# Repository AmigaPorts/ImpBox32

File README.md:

# ImpBox32

<center></center>

This device provides wireless connectivity to your Amiga.
The primary purpose is for use with [IMP](http://aminet.net/package/mus/play/imp3), but with proper firmware it can act as general-purpose network interface.

## Using the IMP firmware

### Flashing the device

Flash the device with firmware from `firmware_impbox` directory - you can use RX/TX pin header for this using typical ESP32 tooling.
Assuming that your COM port is /dev/ttyUSB0:

```plain
esptool --chip esp32 --port /dev/ttyUSB0 --baud 921600 --before default_reset --after hard_reset write_flash -z --flash_mode dio --flash_freq 80m --flash_size 4MB \
0x1000 bootloader.bin \
0x8000 partitions.bin \
0xe000 boot_app0.bin \
0x10000 fw_36.bin
```

The IMP firmware automatically updates itself, so you need to flash it manually only once.

### Using with IMP3

The firmware makes use of SD1306 or compatible OLED I2C display - be sure to connect one at least during registration and configuration phase.

The IMP firmware requires inputing registration key.
If you've built the device for yourself, contact Juen on EAB for getting one.
If you're considering building and selling a batch of devices, ask Juen first to discuss terms on getting keys for them.
See messages displayed on OLED for detailed instructions on how to enter your key.

to configure WiFi network, use following commands:

```plain
imp3 ibcs your_ssid
imp3 ibcp your_password
imp3 ibcc your_key
```

Device stores the key as well as network parameters in its flash memory, hence configuration needs to be done only once.
Once configured, to launch IMP, type:

```plain
imp3 ib
```

## Differences between PCB revisions

Be sure to use the latest PCB revision - old ones are buggy and not supported.

The board currently recommended by IMP authors is rev3.
There's also rev3s board with SD card slot which cauld be made to work with modified sdbox firmware, and will be eventually suported by the universal firmware.

## Using the universal firmware

TBD - this firmware is currently not available.

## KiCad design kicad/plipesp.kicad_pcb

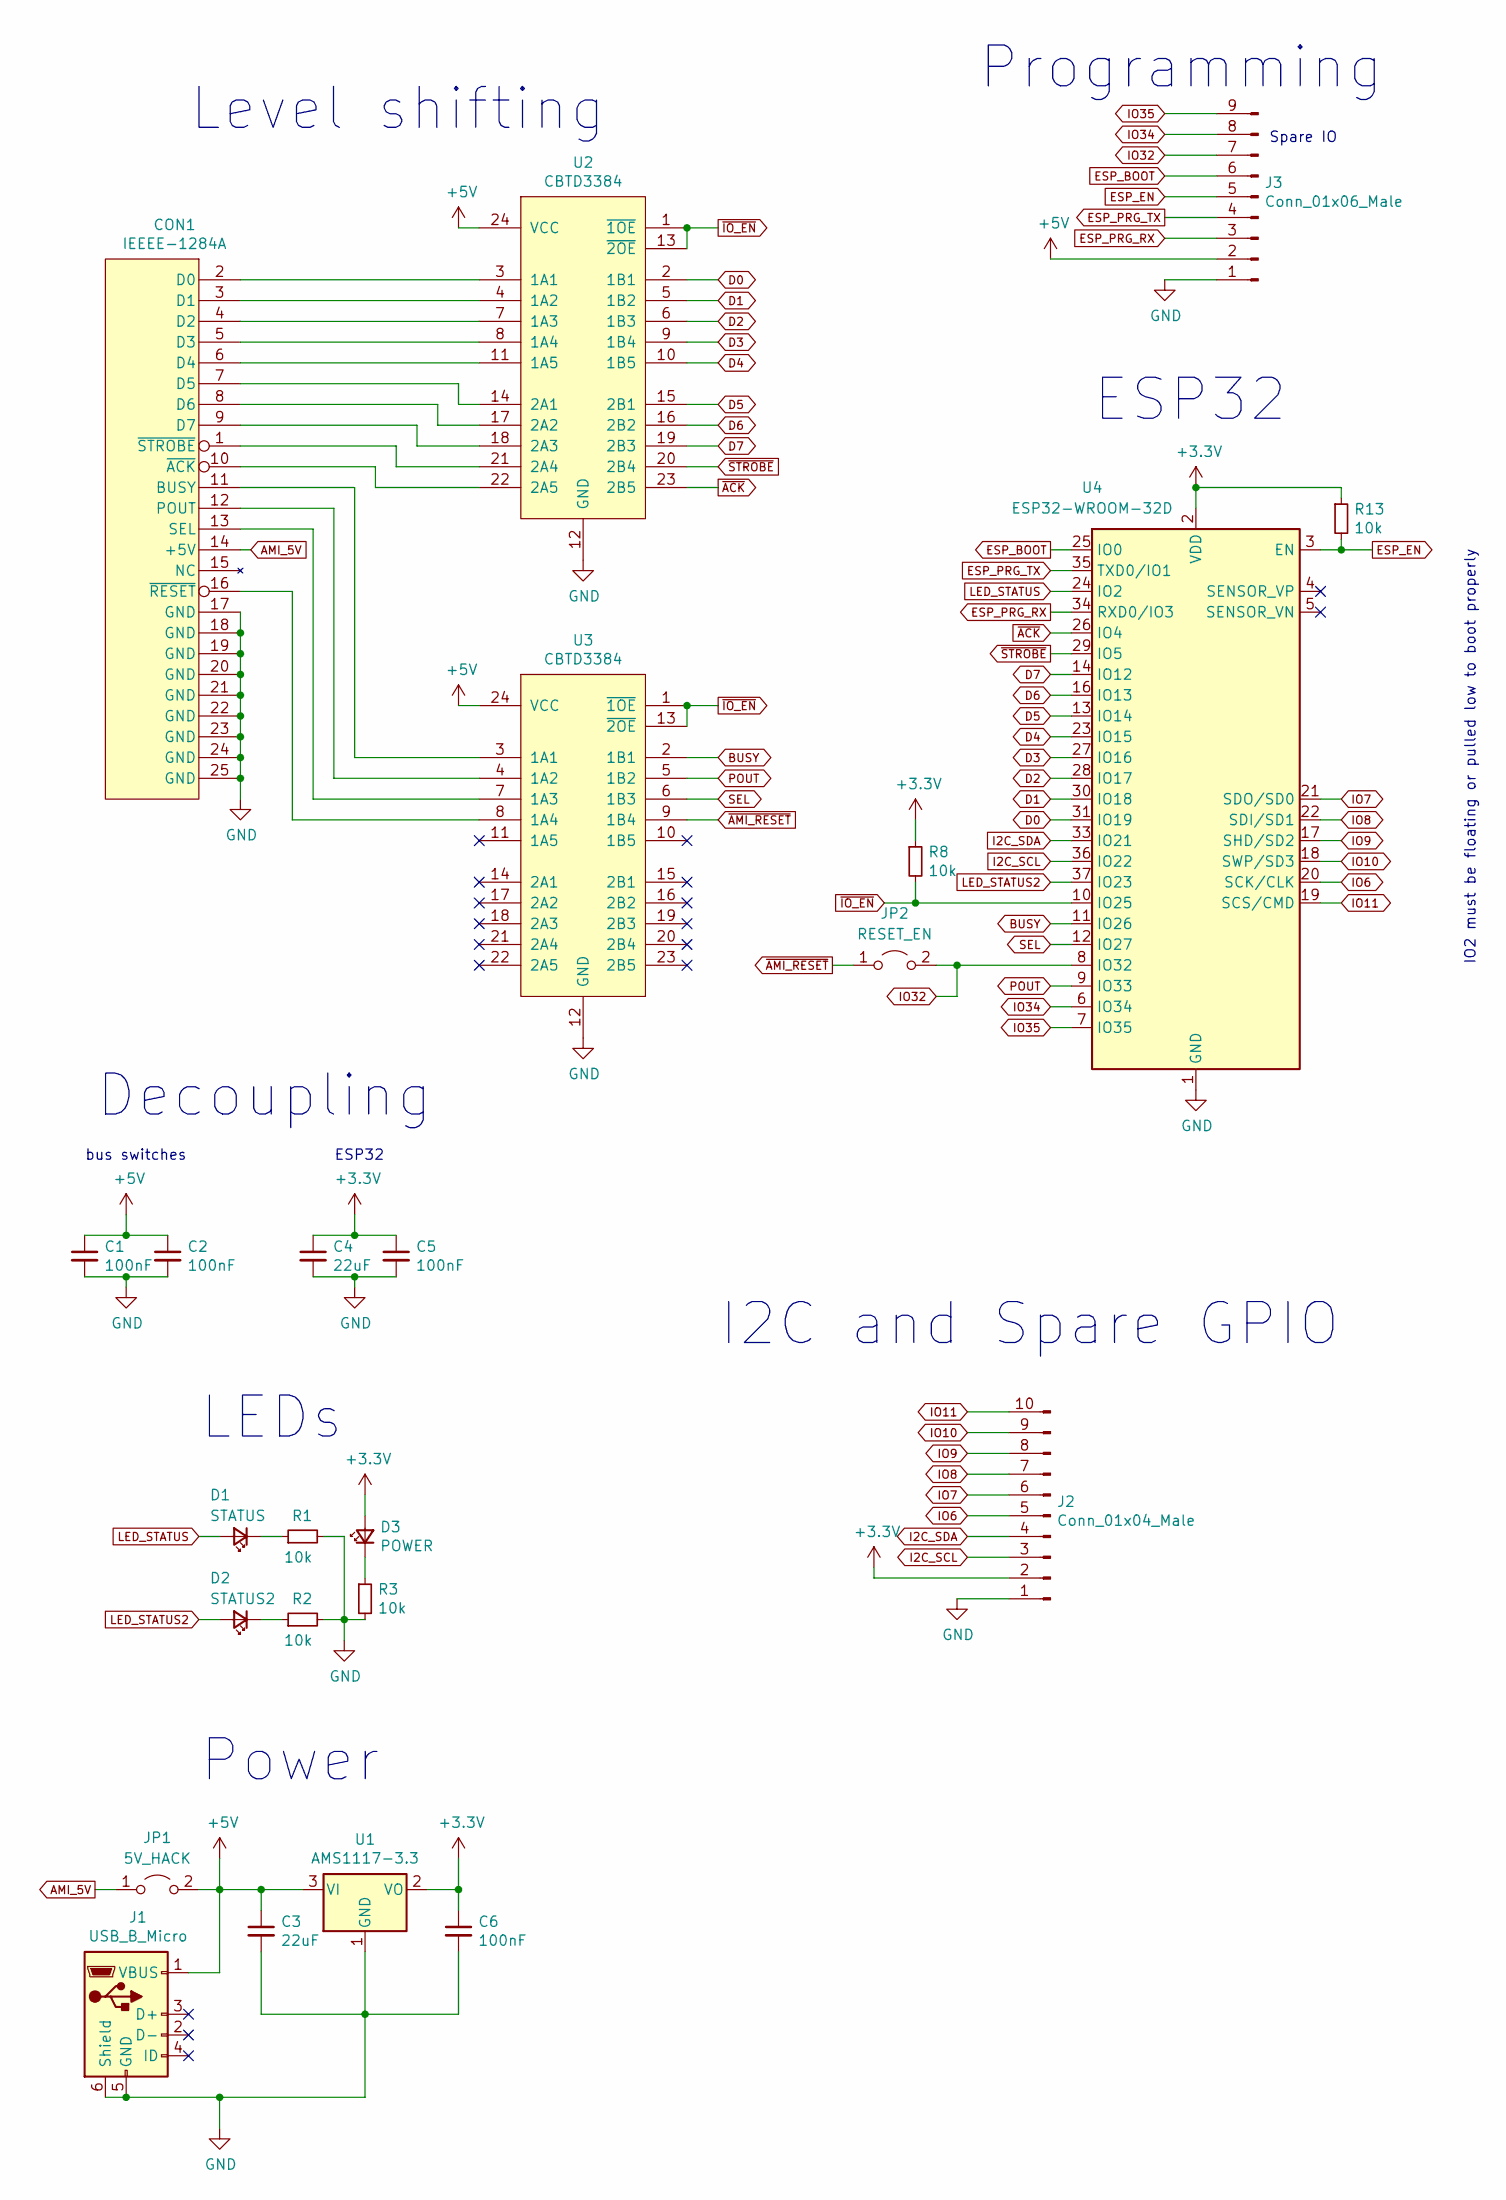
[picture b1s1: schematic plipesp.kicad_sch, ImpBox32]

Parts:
C1, C2, C5, C6: 100nF; C_0805_2012Metric
C3, C4: 22uF; C_1206_3216Metric
CON1: IEEEE-1284A; d-sub25_edge
D1: STATUS; LED_0805_2012Metric
D2: STATUS2; LED_0805_2012Metric
D3: POWER; LED_0805_2012Metric
J1: USB_B_Micro; USB_Micro-B_Amphenol_10103594-0001LF_Horizontal
J2: Conn_01x04_Male; PinHeader_1x10_P2.54mm_Vertical
J3: Conn_01x06_Male; PinHeader_1x09_P2.54mm_Vertical
JP1: 5V_HACK; SolderJumper-2_P1.3mm_Open_RoundedPad1.0x1.5mm
JP2: RESET_EN; SolderJumper-2_P1.3mm_Open_RoundedPad1.0x1.5mm
R1, R2, R3, R8, R13: 10k; R_0805_2012Metric
U1: AMS1117-3.3; SOT-223-3_TabPin2
U2, U3: CBTD3384; SO-universal-24_P0.65mm
U4: ESP32-WROOM-32D; ESP32-WROOM-32

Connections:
+3V3: C4.1, C5.1, C6.1, D3.2 (A), J2.2, R8.1, R13.1, U1.2 (VO), U4.2 (VDD)
+5V: C1.1, C2.1, C3.1, J1.1 (VBUS), J3.2, JP1.2 (B), U1.3 (VI), U2.24 (VCC), U3.24 (VCC)
AMI_5V: CON1.14 (+5V), JP1.1 (A)
BUSY: U3.2 (1B1), U4.11 (IO26)
D0: U2.2 (1B1), U4.31 (IO19)
D1: U2.5 (1B2), U4.30 (IO18)
D2: U2.6 (1B3), U4.28 (IO17)
D3: U2.9 (1B4), U4.27 (IO16)
D4: U2.10 (1B5), U4.23 (IO15)
D5: U2.15 (2B1), U4.13 (IO14)
D6: U2.16 (2B2), U4.16 (IO13)
D7: U2.19 (2B3), U4.14 (IO12)
ESP_BOOT: J3.6, U4.25 (IO0)
ESP_EN: J3.5, R13.2, U4.3 (EN)
ESP_PRG_RX: J3.3, U4.34 (RXD0/IO3)
ESP_PRG_TX: J3.4, U4.35 (TXD0/IO1)
GND: C1.2, C2.2, C3.2, C4.2, C5.2, C6.2, CON1.17 (GND), CON1.18 (GND), CON1.19 (GND), CON1.20 (GND), CON1.21 (GND), CON1.22 (GND), CON1.23 (GND), CON1.24 (GND), CON1.25 (GND), J1.5 (GND), J1.6 (Shield), J2.1, J3.1, R1.2, R2.2, R3.2, U1.1 (GND), U2.12 (GND), U3.12 (GND), U4.1 (GND), U4.15 (GND), U4.38 (GND), U4.39 (GND)
I2C_SCL: J2.3, U4.36 (IO22)
I2C_SDA: J2.4, U4.33 (IO21)
IO6: J2.5, U4.20 (SCK/CLK)
IO7: J2.6, U4.21 (SDO/SD0)
IO8: J2.7, U4.22 (SDI/SD1)
IO9: J2.8, U4.17 (SHD/SD2)
IO10: J2.9, U4.18 (SWP/SD3)
IO11: J2.10, U4.19 (SCS/CMD)
IO32: J3.7, JP2.2 (B), U4.8 (IO32)
IO34: J3.8, U4.6 (IO34)
IO35: J3.9, U4.7 (IO35)
LED_STATUS: D1.2 (A), U4.24 (IO2)
LED_STATUS2: D2.2 (A), U4.37 (IO23)
unnamed: CON1.1 (~STROBE), U2.21 (2A4)
unnamed: CON1.2 (D0), U2.3 (1A1)
unnamed: CON1.3 (D1), U2.4 (1A2)
unnamed: CON1.4 (D2), U2.7 (1A3)
unnamed: CON1.5 (D3), U2.8 (1A4)
unnamed: CON1.6 (D4), U2.11 (1A5)
unnamed: CON1.7 (D5), U2.14 (2A1)
unnamed: CON1.8 (D6), U2.17 (2A2)
unnamed: CON1.9 (D7), U2.18 (2A3)
unnamed: CON1.10 (~ACK), U2.22 (2A5)
unnamed: CON1.11 (BUSY), U3.3 (1A1)
unnamed: CON1.12 (POUT), U3.4 (1A2)
unnamed: CON1.13 (SEL), U3.7 (1A3)
unnamed: CON1.16 (~RESET), U3.8 (1A4)
unnamed: D1.1 (K), R1.1
unnamed: D2.1 (K), R2.1
unnamed: D3.1 (K), R3.1
POUT: U3.5 (1B2), U4.9 (IO33)
SEL: U3.6 (1B3), U4.12 (IO27)
~ACK: U2.23 (2B5), U4.26 (IO4)
~AMI_RESET: JP2.1 (A), U3.9 (1B4)
~IO_EN: R8.2, U2.1 (~1OE), U2.13 (~2OE), U3.1 (~1OE), U3.13 (~2OE), U4.10 (IO25)
~STROBE: U2.20 (2B4), U4.29 (IO5)

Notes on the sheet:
bus switches
IO2 must be floating or pulled low to boot properly
I2C and Spare GPIO
ESP32
Programming
LEDs
Spare IO
Power
Decoupling
Level shifting

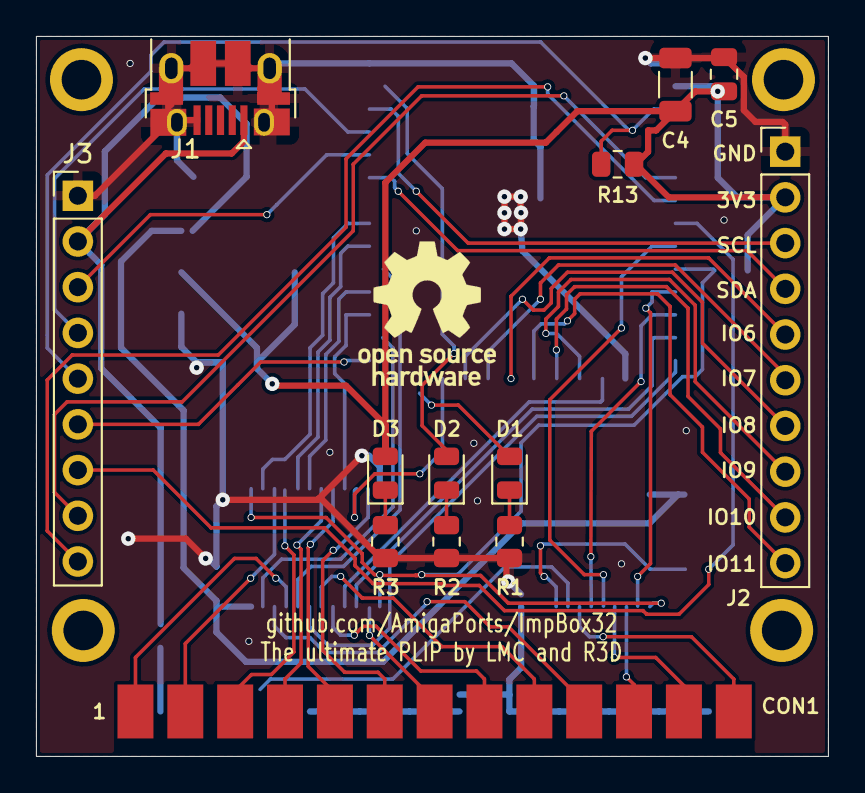
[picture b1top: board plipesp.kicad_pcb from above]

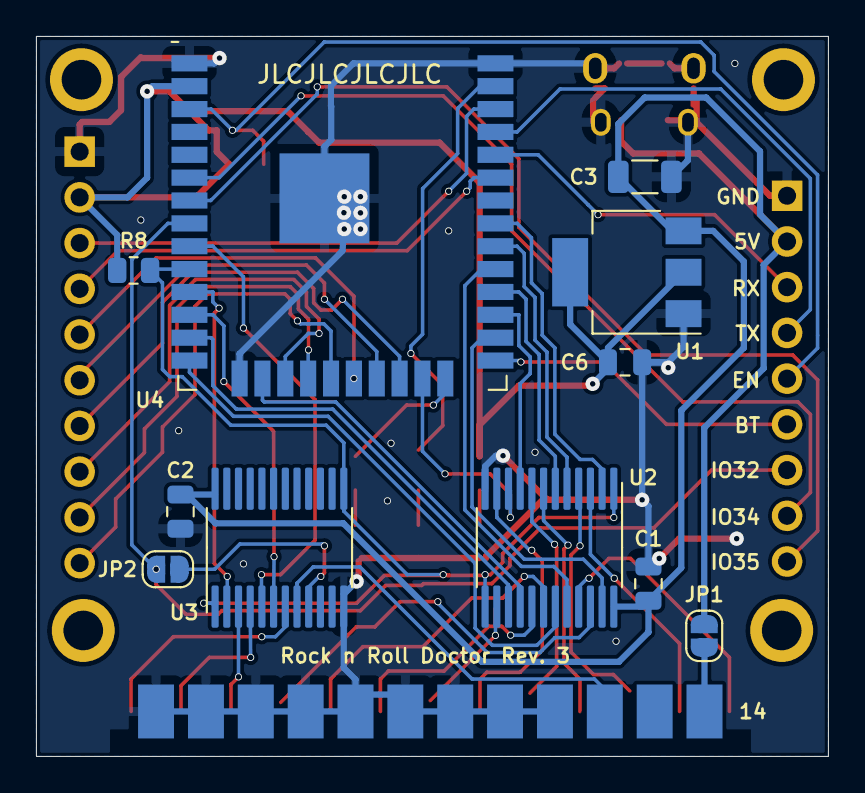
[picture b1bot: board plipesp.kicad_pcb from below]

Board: 2 copper layers, 44.0 x 40.0 mm, 28 parts (11 on the bottom side), 53 nets.

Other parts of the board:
REF1, REF2, REF3, REF4: mounting_hole

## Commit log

2022-06-09 board rev1
2022-06-11 board rev2
2022-08-28 rev3s - with SD card
2022-08-28 rev3 - without SD card, AMI_RESET optional, extra IO on pins
2022-10-28 added IMP firmware, updated flashing steps in readme
2022-10-30 upload full fw
    Full firmware package to upload into fresh ESP32
2022-11-13 Update README.md
    fixed fw name, and correct arduino bootloader, partitions, boot_app files
2022-11-14 Update README.md
    ibcc key command info
2025-12-08 Update info on getting the keys for Impbox
    as per Juen's request/suggestions
